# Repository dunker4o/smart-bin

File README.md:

# Smart Bin
Project for handsfree bin interaction and Wireless data reporting. More Readme updates to follow soon.

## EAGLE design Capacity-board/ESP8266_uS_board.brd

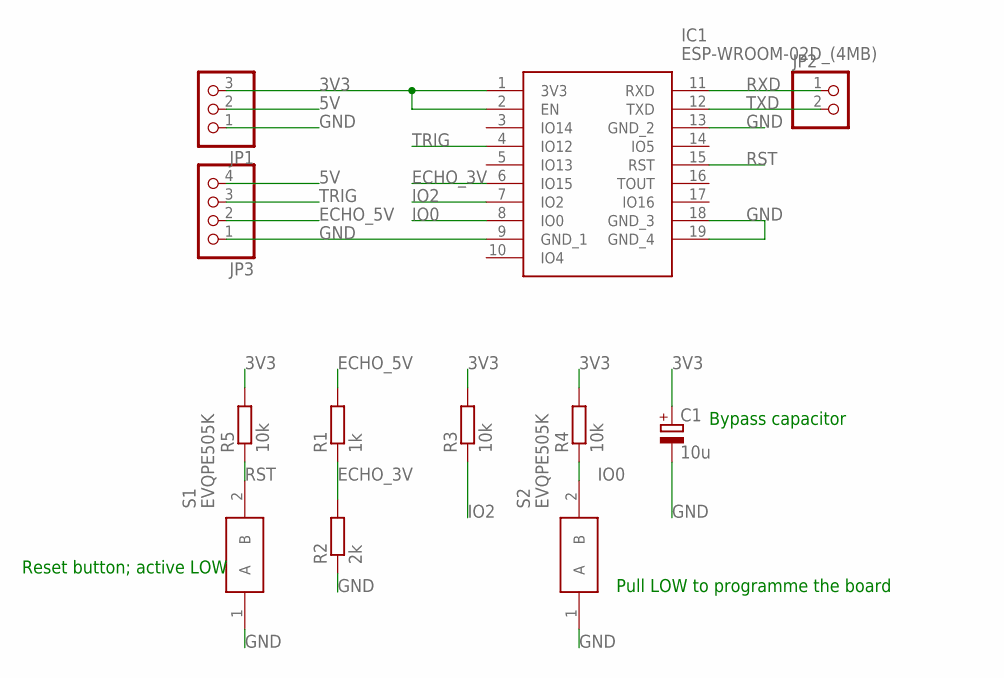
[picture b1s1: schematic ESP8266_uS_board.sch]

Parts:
C1: 10u; D/7343-31R
IC1: ESP-WROOM-02D_(4MB); ESPWROOM02D
JP1: PINHD-1X3; 1X03
JP2: PINHD-1X2; 1X02
JP3: PINHD-1X4; 1X04
R1: 1k; R0805
R2: 2k; R0805
R3, R4, R5: 10k; R0805
S1, S2: EVQPE505K

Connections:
3V3: C1.+, IC1.1 (3V3), IC1.2 (EN), JP1.3, R3.2, R4.2, R5.2
5V: JP1.2, JP3.4
ECHO_3V: IC1.6 (IO15), R1.1, R2.2
ECHO_5V: JP3.2, R1.2
GND: C1.-, IC1.9 (GND_1), IC1.13 (GND_2), IC1.18 (GND_3), IC1.19 (GND_4), JP1.1, JP3.1, R2.1, S1.1 (A), S2.1 (A)
IO0: IC1.8 (IO0), R4.1, S2.2 (B)
IO2: IC1.7 (IO2), R3.1
RST: IC1.15 (RST), R5.1, S1.2 (B)
RXD: IC1.11 (RXD), JP2.1
TRIG: IC1.4 (IO12), JP3.3
TXD: IC1.12 (TXD), JP2.2

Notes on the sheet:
Reset button; active LOW
Pull LOW to programme the board
Bypass capacitor

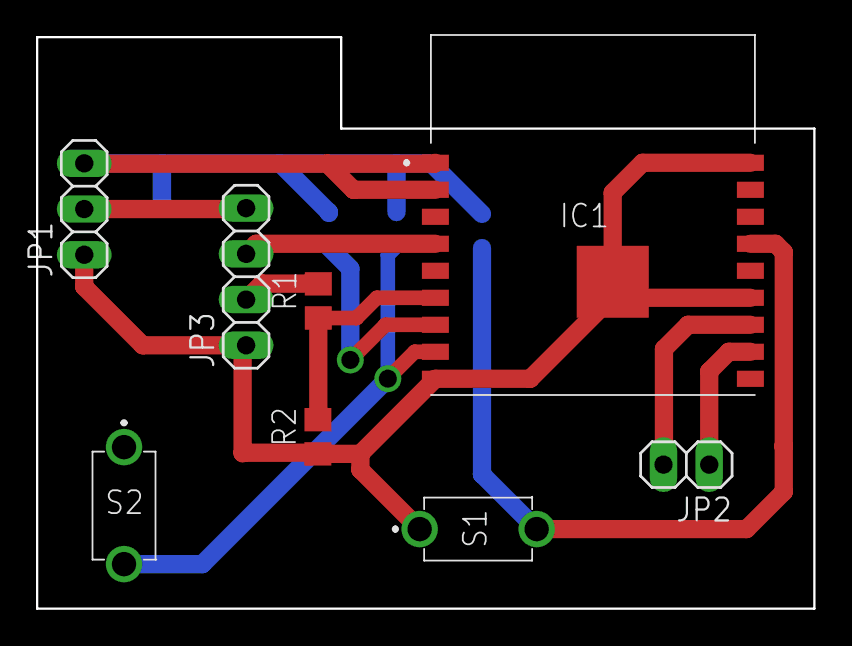
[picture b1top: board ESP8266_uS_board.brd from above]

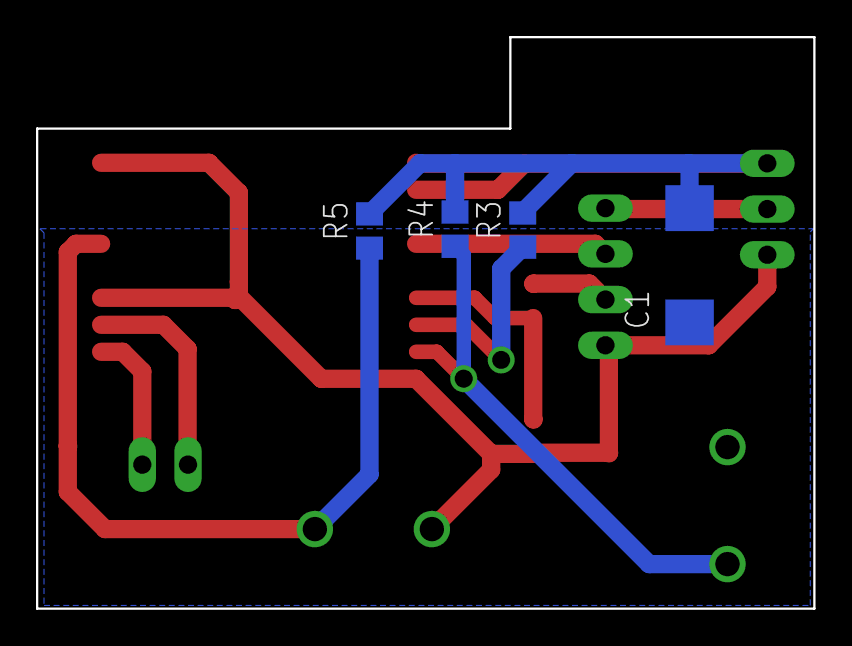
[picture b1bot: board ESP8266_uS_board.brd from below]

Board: 2 copper layers, 43.2 x 31.8 mm, 12 parts (4 on the bottom side), 11 nets.

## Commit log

2019-04-21 Added schematics and PCB for ESP8266 board that senses how full the bin is.
2019-04-21 Added board dimensions to the image.:
2019-04-21 Added initial sketch for the ESP8266 that would handle requests from clients.
2019-04-22 Added sensor reading and transmitting over html on HTTP request.
2019-04-24 Added phone app that scrapes the selected web address for a valid html page and parses the data for display.
2019-04-26 Added sketch for main Arduino board that senses approach and opens bin.
2019-04-28 Changed phone app to connect to ESP's IP. ESP board code now works with ESP12 breakout.
2019-04-28 Added a settings screen which now allows the user to change bin IP. It also has a few general unused setting.
2019-04-29 Added initial files for integration to Home Assistant.
2019-04-29 Added more files for Home Assistant integration.
2019-04-29 Added custom app logo.
2019-04-30 Bin app now succesfully displays how full is the bin. It also has the option of displaying debug information (readings). Works ok. TODO: Add percentage field.
2019-04-30 Added notifications and percentage display to the app.
2019-04-30 Added option of switching on/off percentage.
2019-04-30 Option now toggles between text and percentage display.
2019-04-30 Added Bin name to notification.
2019-05-17 Removed obsolete files from Home Assistant integration. Updated missing dependancy.
2019-05-17 Added Android application APK file.
2019-05-17 Lowered the minimum sdkVersion for the build
